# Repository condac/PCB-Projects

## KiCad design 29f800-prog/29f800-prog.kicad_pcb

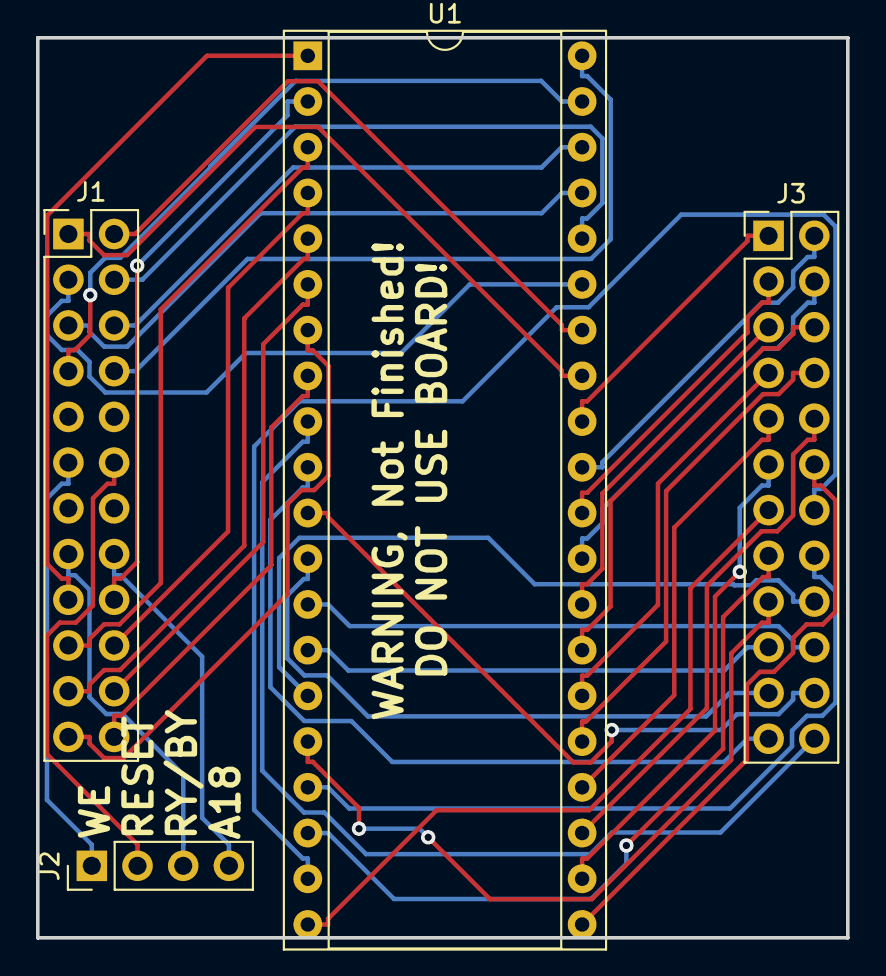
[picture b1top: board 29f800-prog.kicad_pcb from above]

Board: 2 copper layers, 45.0 x 50.0 mm, 4 parts (0 on the bottom side), 44 nets.

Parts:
J1, J3: Conn_02x12_Odd_Even; PinHeader_2x12_P2.54mm_Vertical
J2: Conn_01x04; PinHeader_1x04_P2.54mm_Vertical
U1: AmigaSocket; DIP-40_W15.24mm_Socket

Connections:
/P1: J1.1, U1.33
/P2: J1.2, U1.34
/P3: J1.3, U1.35
/P4: J1.4, U1.36
/P5: J1.5, U1.37
/P6: J1.6, U1.38
/P7: J1.7, U1.39
/P8: J1.8, U1.40
/P11: J1.11, J2.1
/P12: J1.12, J2.2
/P15: J1.15, J2.3
/P16: J1.16, J2.4
/P17: J1.17, U1.1
/P18: J1.18, U1.2
/P19: J1.19, U1.3
/P20: J1.20, U1.4
/P21: J1.21, U1.5
/P22: J1.22, U1.6
/P23: J1.23, U1.7
/P24: J1.24, U1.8
/P25: J3.24, U1.9
/P26: J3.23, U1.10
/P27: J3.22, U1.11
/P28: J3.21, U1.12
/P29: J3.20, U1.13
/P30: J3.19, U1.14
/P31: J3.18, U1.15
/P32: J3.17, U1.16
/P33: J3.16, U1.17
/P34: J3.15, U1.18
/P35: J3.14, U1.19
/P36: J3.13, U1.20
/P37: J3.12, U1.21
/P38: J3.11, U1.22
/P39: J3.10, U1.23
/P40: J3.9, U1.24
/P41: J3.8, U1.25
/P42: J3.7, U1.26
/P43: J3.6, U1.27
/P44: J3.5, U1.28
/P45: J3.4, U1.29
/P46: J3.3, U1.30
/P47: J3.2, U1.31
/P48: J3.1, U1.32

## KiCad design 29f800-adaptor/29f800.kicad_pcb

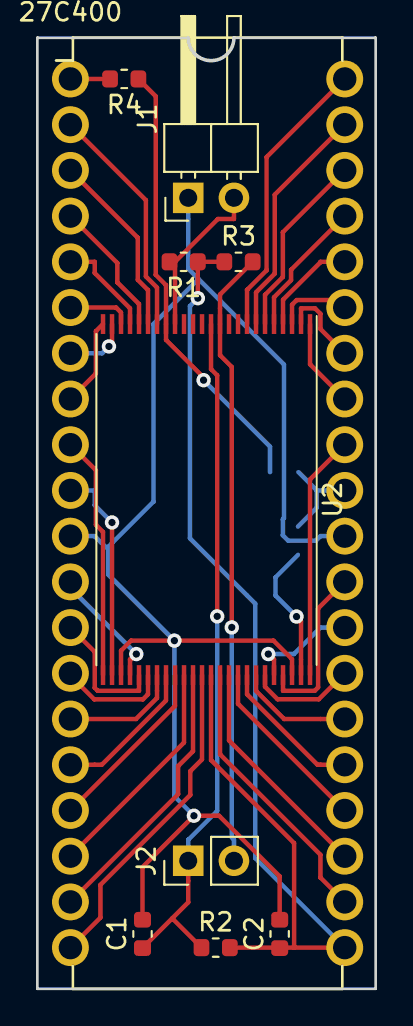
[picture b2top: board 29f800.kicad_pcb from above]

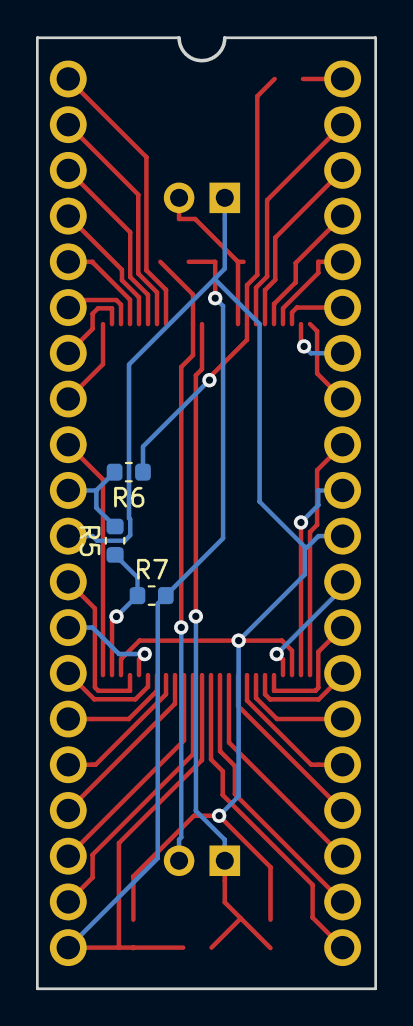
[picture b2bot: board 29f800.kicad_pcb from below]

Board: 2 copper layers, 18.7 x 52.8 mm, 13 parts (3 on the bottom side), 44 nets.

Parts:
C1, C2: 0.1uF; C_0603_1608Metric
J1: Conn_01x02; PinHeader_1x02_P2.54mm_Horizontal
J2: Conn_01x02; PinHeader_1x02_P2.54mm_Vertical
R1, R2, R3: 10K; R_0603_1608Metric
R4, R5, R6: 0; R_0603_1608Metric
R7: 10k; R_0603_1608Metric
U1: 27C400
U2: 29F800; TSOP-I-48_18.4x12mm_P0.5mm

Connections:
/P1_1: R4.2, U1.1
/P1_2: R4.1, R6.1, U2.17
/P2: U1.2, U2.18
/P3: U1.3, U2.19
/P4: U1.4, U2.20
/P5: U1.5, U2.21
/P6: U1.6, U2.22
/P7: U1.7, U2.23
/P8: U1.8, U2.24
/P9: U1.9, U2.25
/P10: U1.10, U2.26
/P12: U1.12, U2.28
/P13: U1.13, U2.29
/P14: U1.14, U2.30
/P15: U1.15, U2.31
/P16: U1.16, U2.32
/P17: U1.17, U2.33
/P18: U1.18, U2.34
/P19: U1.19, U2.35
/P20: U1.20, U2.36
/P22: U1.22, U2.38
/P23: U1.23, U2.39
/P24: U1.24, U2.40
/P25: U1.25, U2.41
/P26: U1.26, U2.42
/P27: U1.27, U2.43
/P28: U1.28, U2.44
/P29: U1.29, U2.45
/P31_1: R5.2, R6.2, U1.31
/P31_2: R5.1, R7.1, U2.47
/P32: U1.32, U2.48
/P33: U1.33, U2.1
/P34: U1.34, U2.2
/P35: U1.35, U2.3
/P36: U1.36, U2.4
/P37: U1.37, U2.5
/P38: U1.38, U2.6
/P39: U1.39, U2.7
/P40: U1.40, U2.8
/P_A18: J1.2, R1.2, U2.16
/P_RST: C1.1, J2.1, R2.1, U2.12
/P_WE: J2.2, R3.2, U2.11
VCC: C2.1, R1.1, R2.2, R3.1, R7.2, U1.21, U2.37
VSS: C1.2, C2.2, J1.1, U1.11, U1.30, U2.27, U2.46

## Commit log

2018-10-09 Created adapter for 29f800
2018-10-11 KiCad 5 libs for 29f800 adapter
2018-10-11 ReRouted after KiCad 5 libs because of bigger footprint
2018-10-12 Added resistors and layout for A500 routing bug
2018-10-12 Created adapter from 29f800 to tl866 programmer
2018-10-14 Programming adapter
